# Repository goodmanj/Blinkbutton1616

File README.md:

# Blinkbutton 1616
A simple countdown timer board using an ATTiny1616 microcontroller.

A 10-second countdown timer based on an ATTiny1616.  Board based on Neil Gershenfeld's [hello.t1614.echo](http://academy.cba.mit.edu/classes/embedded_programming/index.html).  Use Spence Konde's [megaTinyCore](https://github.com/SpenceKonde/megaTinyCore) Arduino core to compile Arduino code.  The board can also be programmed to do other things involving a button and two LEDs...

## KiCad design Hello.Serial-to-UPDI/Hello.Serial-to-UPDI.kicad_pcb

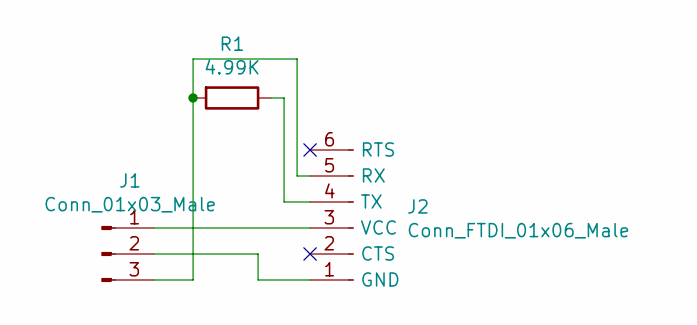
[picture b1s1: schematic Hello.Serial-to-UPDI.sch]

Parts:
J1: Conn_01x03_Male; Header_SMD_01x03_P2.54mm_Horizontal_Male
J2: Conn_FTDI_01x06_Male; Header_SMD_FTDI_01x06_P2.54mm_Horizontal_Male
R1: 4.99K; R_1206

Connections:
unnamed: J1.1, J2.3 (VCC)
unnamed: J1.2, J2.1 (GND)
unnamed: J1.3, J2.5 (RX), R1.2
unnamed: J2.4 (TX), R1.1

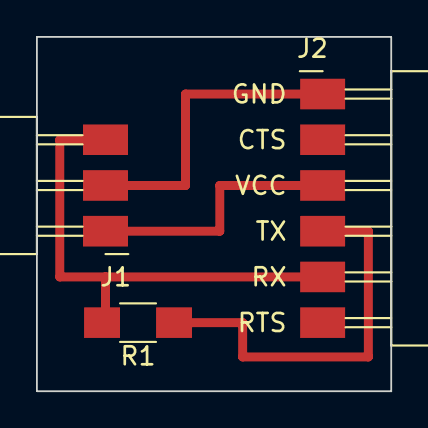
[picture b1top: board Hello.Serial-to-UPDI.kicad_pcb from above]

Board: 2 copper layers, 19.7 x 19.7 mm, 3 parts (0 on the bottom side), 4 nets.

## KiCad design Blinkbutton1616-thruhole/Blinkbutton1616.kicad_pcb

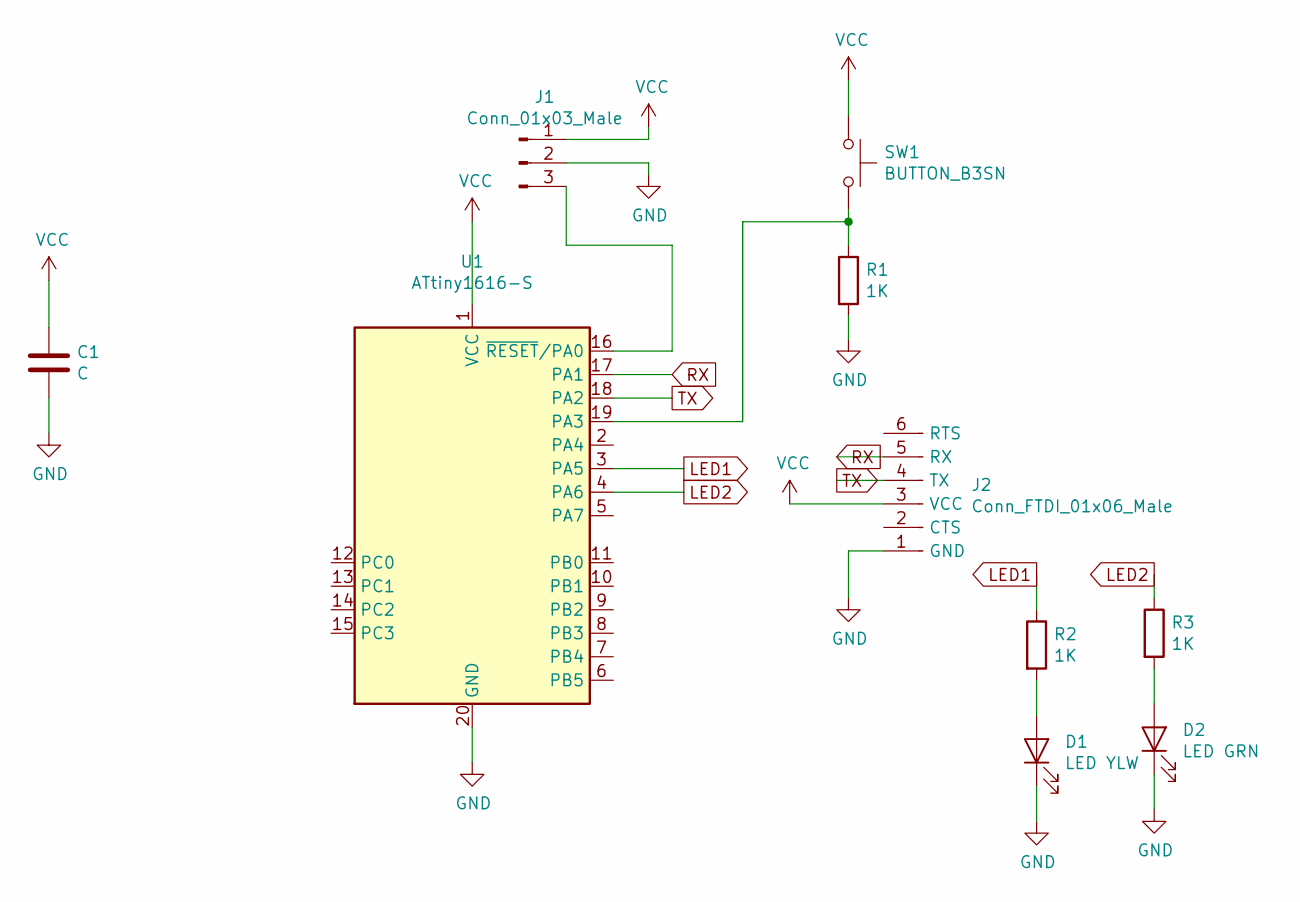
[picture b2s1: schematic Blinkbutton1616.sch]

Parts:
C1: C; fab-C1206
D1: LED YLW; LED_1206
D2: LED GRN; LED_1206
J1: Conn_01x03_Male; PinHeader_1x03_P2.54mm_Horizontal
J2: Conn_FTDI_01x06_Male; PinHeader_1x06_P2.54mm_Vertical
R1, R2, R3: 1K; R_1206
SW1: BUTTON_B3SN; Button_Omron_B3SN_6x6mm
U1: ATtiny1616-S; SOIC-20W_7.5x12.8mm_P1.27mm

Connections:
GND: C1.2, D1.1 (K), D2.1 (K), J1.2, J2.1 (GND), R1.2, U1.20 (GND)
LED1: R2.1, U1.3 (PA5)
LED2: R3.1, U1.4 (PA6)
unnamed: D1.2 (A), R2.2
unnamed: D2.2 (A), R3.2
unnamed: J1.3, U1.16 (~RESET~/PA0)
unnamed: R1.1, SW1.2, U1.19 (PA3)
RX: J2.5 (RX), U1.17 (PA1)
TX: J2.4 (TX), U1.18 (PA2)
VCC: C1.1, J1.1, J2.3 (VCC), SW1.1, U1.1 (VCC)

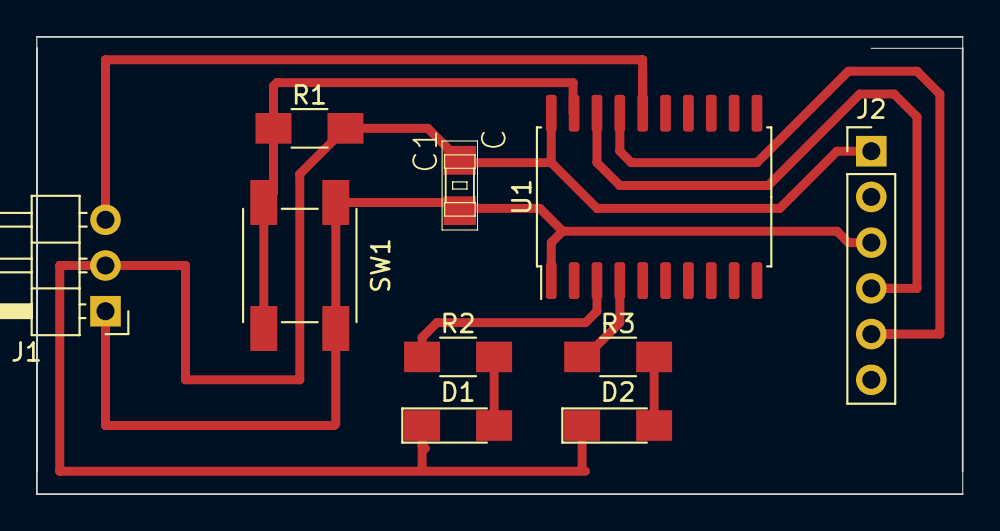
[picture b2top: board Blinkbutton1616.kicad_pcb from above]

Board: 2 copper layers, 51.4 x 25.4 mm, 10 parts (0 on the bottom side), 10 nets.

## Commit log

2021-02-26 Removed serial-to-updi board from repo
2021-02-26 Create README.md
    Wrote README
